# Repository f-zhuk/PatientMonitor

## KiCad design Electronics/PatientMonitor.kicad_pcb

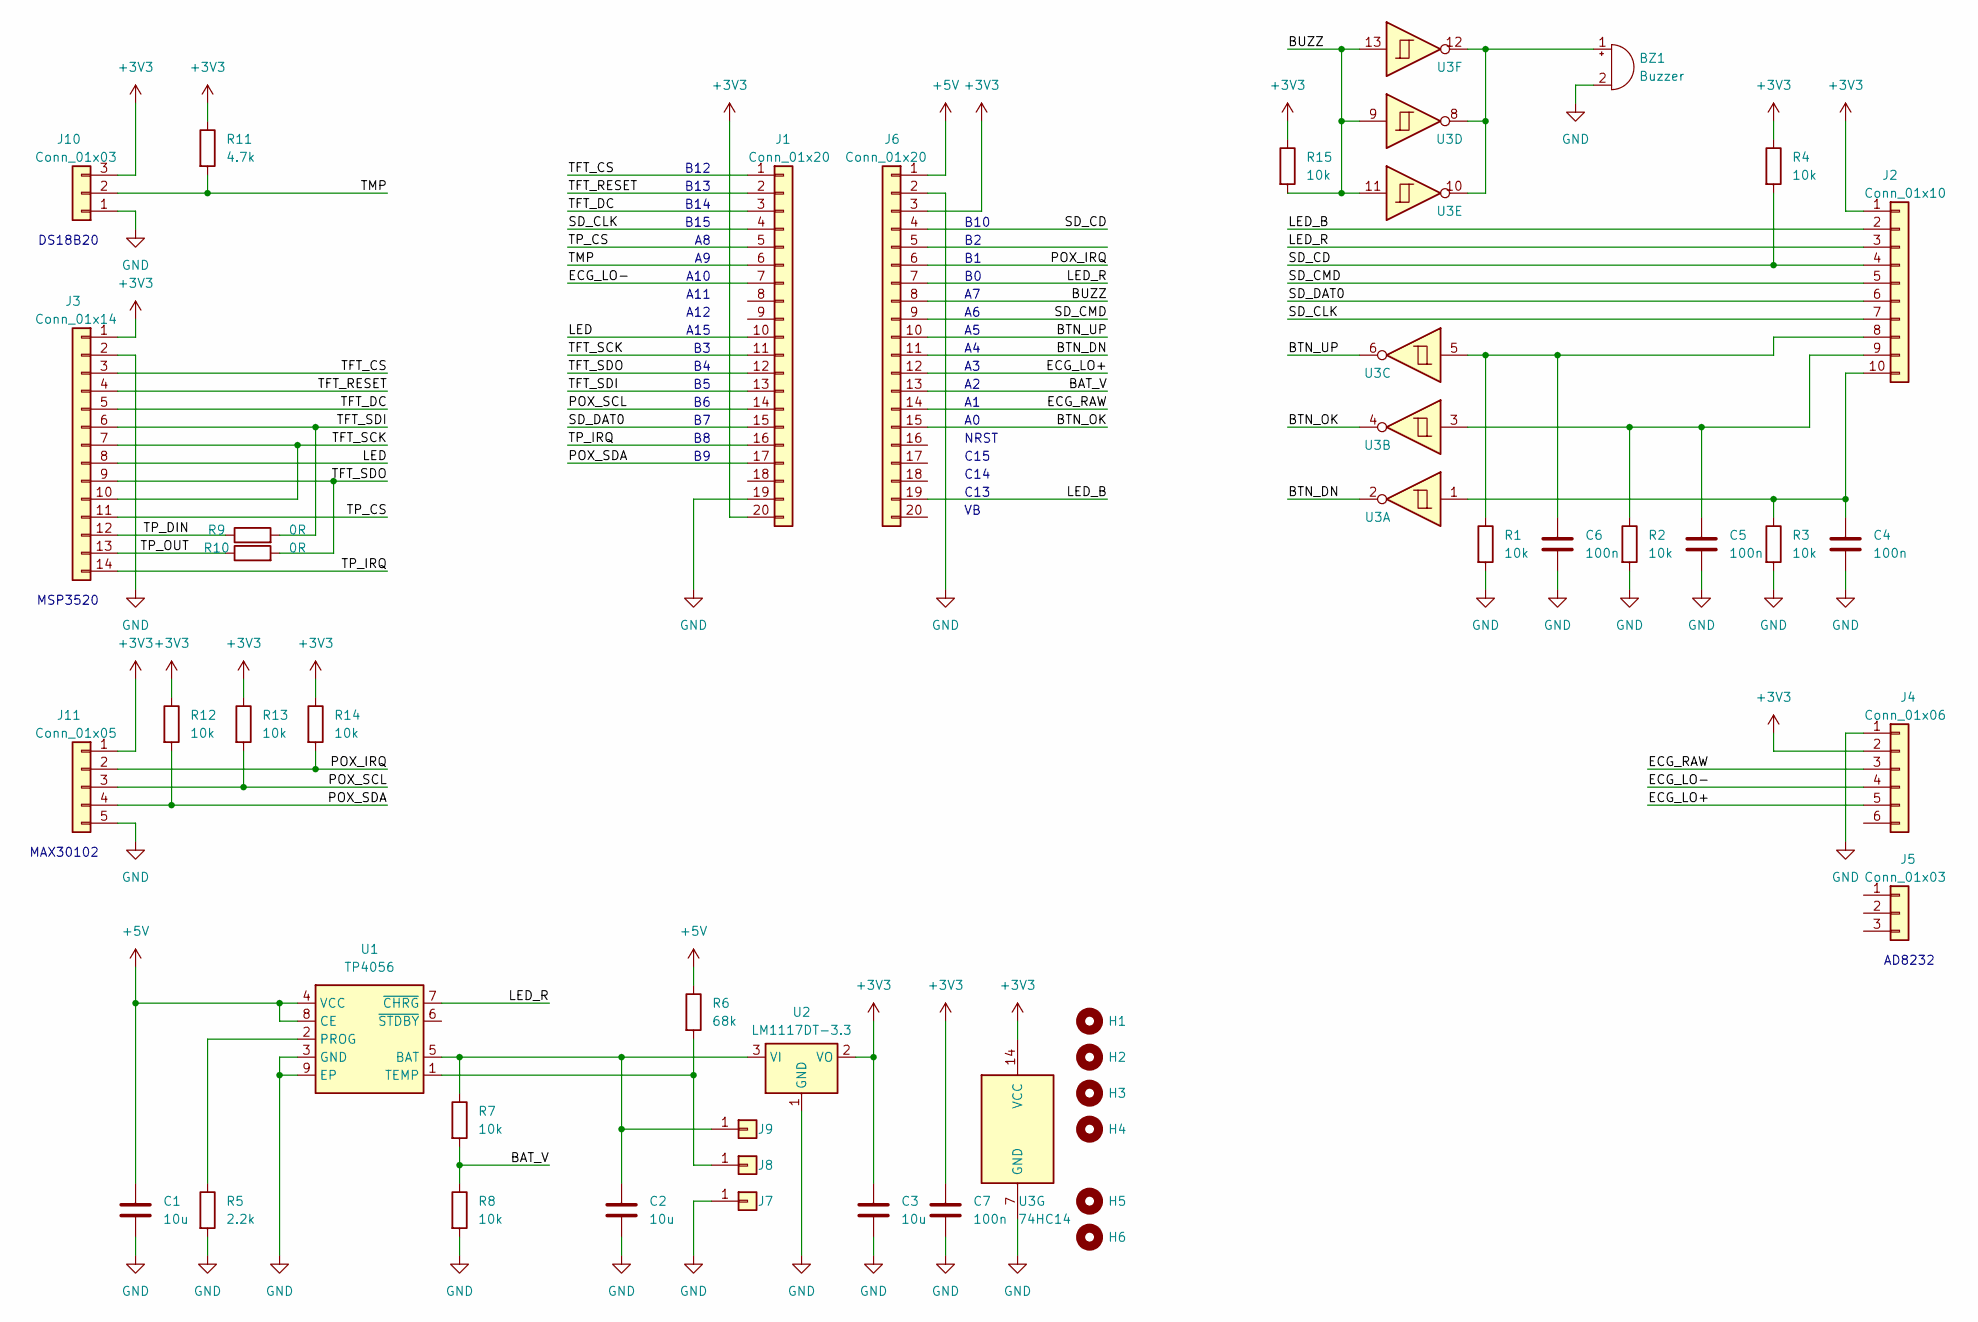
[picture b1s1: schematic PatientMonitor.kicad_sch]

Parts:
BZ1: Buzzer; Buzzer_15x7.5RM7.6
C1, C2, C3: 10u; C_0805_2012Metric_Pad1.18x1.45mm_HandSolder
C4, C5, C6, C7: 100n; C_0603_1608Metric_Pad1.08x0.95mm_HandSolder
H1, H2, H3, H4: MountingHole; MountingHole_3.2mm_M3
H5, H6: MountingHole; MountingHole_3.2mm_M3_Pad
J1, J6: Conn_01x20; PinSocket_1x20_P2.54mm_Vertical
J2: Conn_01x10; PinSocket_1x10_P2.54mm_Vertical
J3: Conn_01x14; PinSocket_1x14_P2.54mm_Vertical
J4: Conn_01x06; PinSocket_1x06_P2.54mm_Vertical
J5, J10: Conn_01x03; PinSocket_1x03_P2.54mm_Vertical
J7, J8, J9: Conn_01x01; SolderWire-0.5sqmm_1x01_D0.9mm_OD2.3mm
J11: Conn_01x05; PinHeader_1x05_P2.54mm_Vertical
R1, R2, R3, R4, R7, R8, R12, R13, R14, R15: 10k; R_0603_1608Metric_Pad0.98x0.95mm_HandSolder
R5: 2.2k; R_0603_1608Metric_Pad0.98x0.95mm_HandSolder
R6: 68k; R_0603_1608Metric_Pad0.98x0.95mm_HandSolder
R9, R10: 0R; R_0603_1608Metric_Pad0.98x0.95mm_HandSolder
R11: 4.7k; R_0603_1608Metric_Pad0.98x0.95mm_HandSolder
U1: TP4056; SOIC-8-1EP_3.9x4.9mm_P1.27mm_EP2.29x3mm
U2: LM1117DT-3.3; TO-252-2
U3: 74HC14; SO-14_3.9x8.65mm_P1.27mm

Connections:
+3V3: C3.1, C7.1, J1.20, J2.1, J3.1, J4.2, J6.3, J10.3, J11.1, R4.1, R11.1, R12.1, R13.1, R14.1, R15.1, U2.2 (VO), U3.14 (VCC)
+5V: C1.1, J6.1, R6.1, U1.4 (VCC), U1.8 (CE)
/BAT_V: J6.13, R7.2, R8.1
/BTN_DN: J6.11, U3.2
/BTN_OK: J6.15, U3.4
/BTN_UP: J6.10, U3.6
/BUZZ: J6.8, R15.2, U3.9, U3.11, U3.13
/ECG_LO+: J4.5, J6.12
/ECG_LO-: J1.7, J4.4
/ECG_RAW: J4.3, J6.14
/LED: J1.10, J3.8
/LED_B: J2.2, J6.19
/LED_R: J2.3, J6.7, U1.7 (~CHRG)
/POX_IRQ: J6.6, J11.2, R14.2
/POX_SCL: J1.14, J11.3, R13.2
/POX_SDA: J1.17, J11.4, R12.2
/SD_CD: J2.4, J6.4, R4.2
/SD_CLK: J1.4, J2.7
/SD_CMD: J2.5, J6.9
/SD_DAT0: J1.15, J2.6
/TFT_CS: J1.1, J3.3
/TFT_DC: J1.3, J3.5
/TFT_RESET: J1.2, J3.4
/TFT_SCK: J1.11, J3.7, J3.10
/TFT_SDI: J1.13, J3.6, R9.2
/TFT_SDO: J1.12, J3.9, R10.2
/TMP: J1.6, J10.2, R11.2
/TP_CS: J1.5, J3.11
/TP_DIN: J3.12, R9.1
/TP_IRQ: J1.16, J3.14
/TP_OUT: J3.13, R10.1
GND: BZ1.2 (-), C1.2, C2.2, C3.2, C4.2, C5.2, C6.2, C7.2, J1.19, J3.2, J4.1, J6.2, J7.1, J10.1, J11.5, R1.2, R2.2, R3.2, R5.2, R8.2, U1.3 (GND), U1.9 (EP), U2.1 (GND), U3.7 (GND)
unnamed: BZ1.1 (+), U3.8, U3.10, U3.12
unnamed: C6.1, J2.8, R1.1, U3.5
unnamed: C5.1, J2.9, R2.1, U3.3
unnamed: C4.1, J2.10, R3.1, U3.1
unnamed: J8.1, R6.2, U1.1 (TEMP)
unnamed: C2.1, J9.1, R7.1, U1.5 (BAT), U2.3 (VI)
unnamed: R5.1, U1.2 (PROG)

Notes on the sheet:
B15
A11
MSP3520
A12
AD8232
B13
B14
MAX30102
NRST
C13
C15
B10
B12
A15
A10
DS18B20
C14

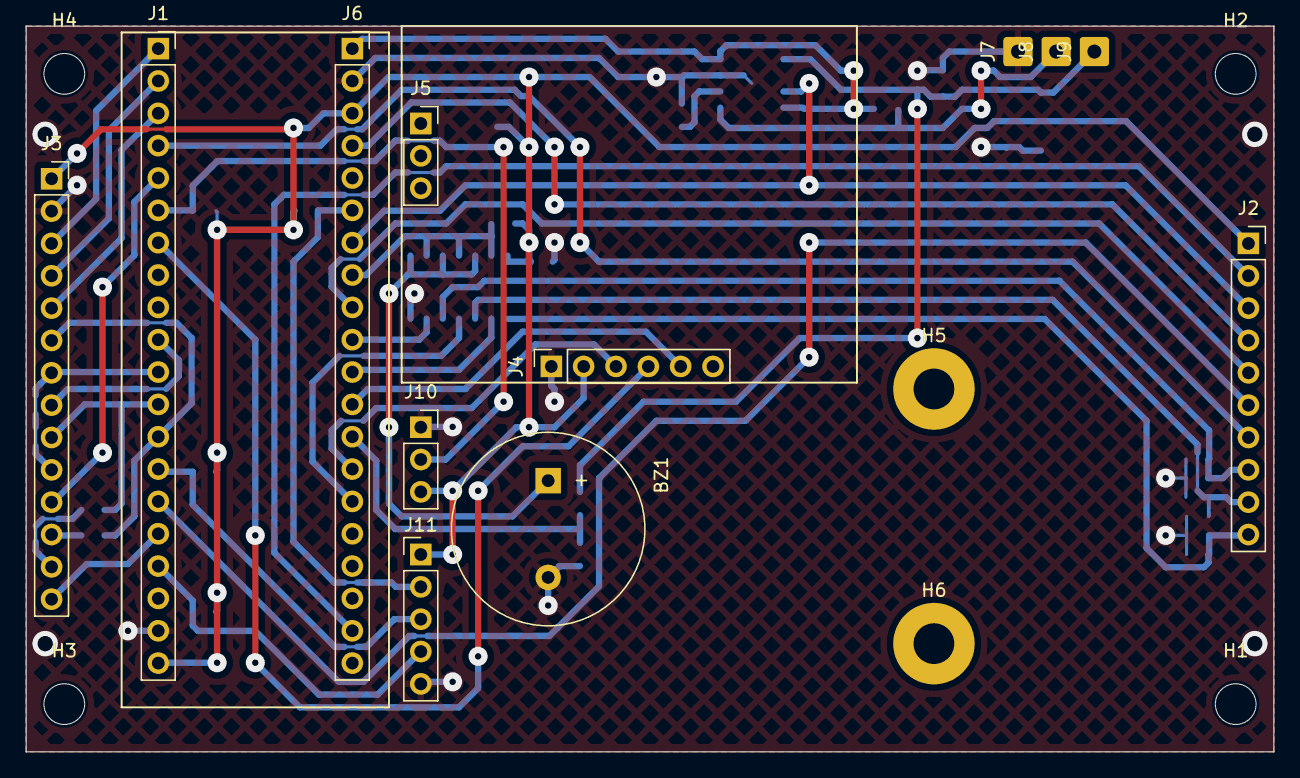
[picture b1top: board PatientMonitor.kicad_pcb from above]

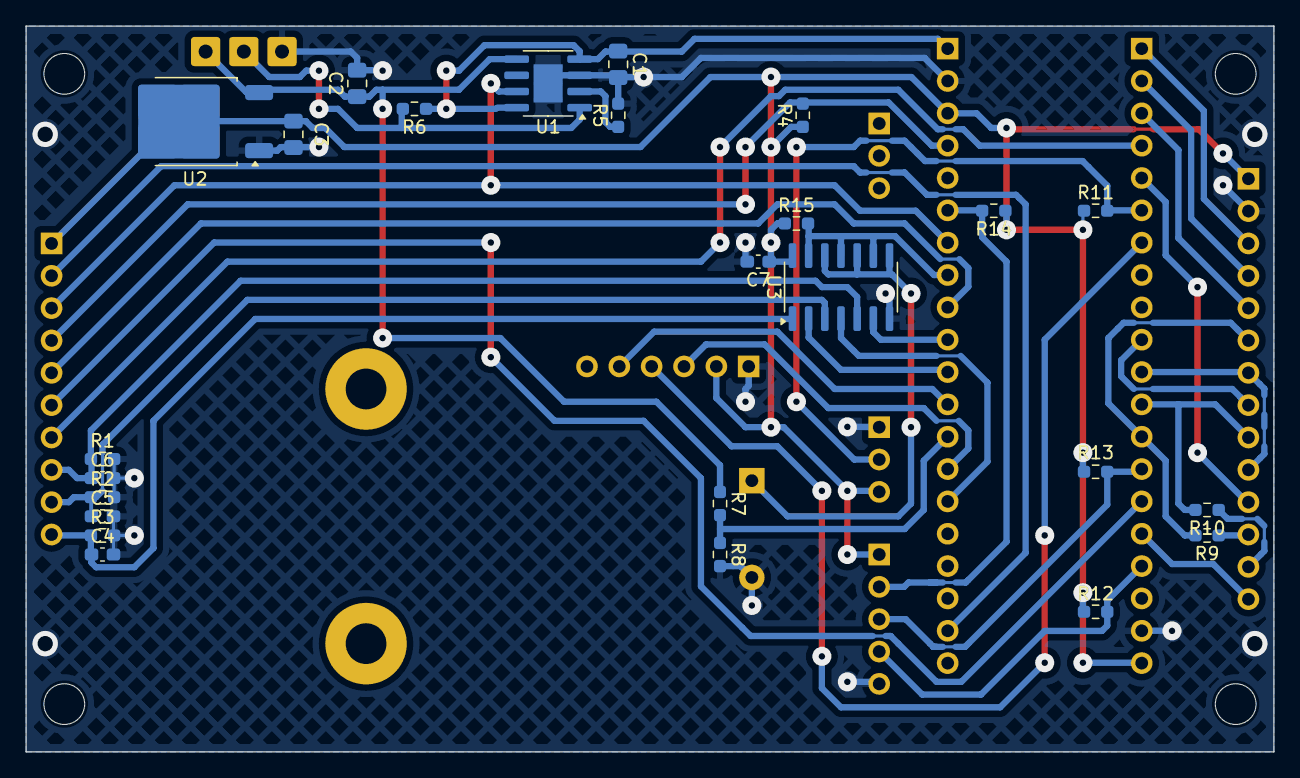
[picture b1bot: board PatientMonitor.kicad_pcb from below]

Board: 2 copper layers, 98.0 x 57.0 mm, 43 parts (25 on the bottom side), 39 nets.

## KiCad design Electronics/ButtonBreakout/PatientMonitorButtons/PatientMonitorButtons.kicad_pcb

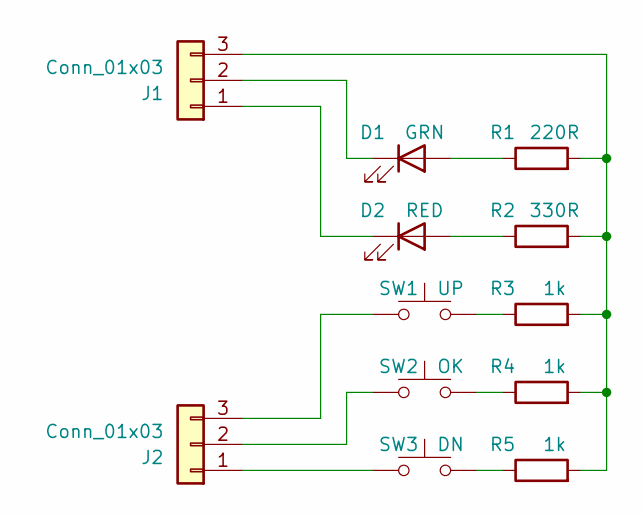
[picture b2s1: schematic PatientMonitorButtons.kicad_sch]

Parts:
D1: GRN; LED_0805_2012Metric_Pad1.15x1.40mm_HandSolder
D2: RED; LED_0805_2012Metric_Pad1.15x1.40mm_HandSolder
J1, J2: Conn_01x03; PinHeader_1x03_P2.54mm_Horizontal
R1: 220R; R_0603_1608Metric_Pad0.98x0.95mm_HandSolder
R2: 330R; R_0603_1608Metric_Pad0.98x0.95mm_HandSolder
R3, R4, R5: 1k; R_0603_1608Metric_Pad0.98x0.95mm_HandSolder
SW1: UP; SW_SPST_CK_PTS641
SW2: OK; SW_SPST_CK_PTS641
SW3: DN; SW_SPST_CK_PTS641

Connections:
unnamed: D1.2 (A), R1.1
unnamed: D1.1 (K), J1.2
unnamed: D2.2 (A), R2.1
unnamed: D2.1 (K), J1.1
unnamed: J1.3, R1.2, R2.2, R3.2, R4.2, R5.2
unnamed: J2.1, SW3.1
unnamed: J2.2, SW2.1
unnamed: J2.3, SW1.1
unnamed: R3.1, SW1.2
unnamed: R4.1, SW2.2
unnamed: R5.1, SW3.2

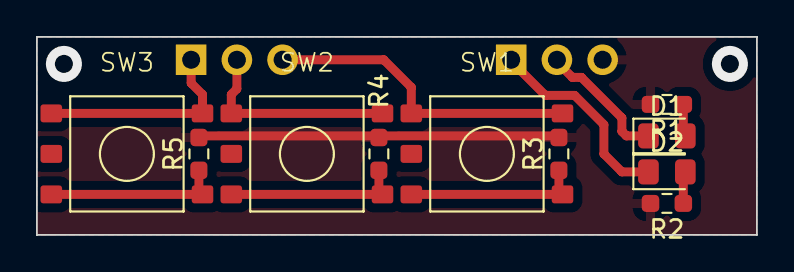
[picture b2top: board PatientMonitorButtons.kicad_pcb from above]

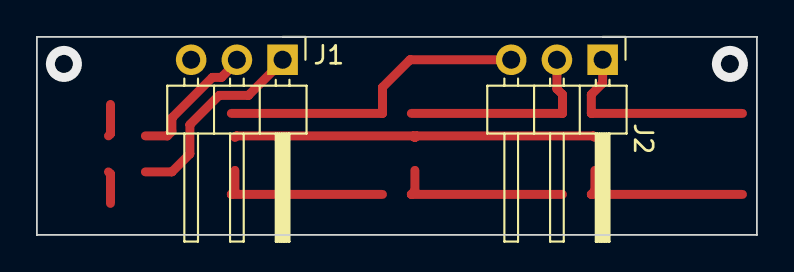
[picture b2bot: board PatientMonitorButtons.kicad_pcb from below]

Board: 2 copper layers, 40.0 x 11.0 mm, 12 parts (2 on the bottom side), 11 nets.

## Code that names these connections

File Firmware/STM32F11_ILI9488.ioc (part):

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Mcu.Name=STM32F411C(C-E)Ux
Mcu.Package=UFQFPN48
Mcu.UserName=STM32F411CEUx
PA0-WKUP.GPIOParameters=GPIO_Label
PA0-WKUP.GPIO_Label=BTN_OK
PA0-WKUP.Mode=SYS_WakeUp0
PA0-WKUP.Signal=SYS_WKUP
PA1.GPIOParameters=GPIO_Label
PA1.GPIO_Label=ECG_RAW
PA1.Signal=ADCx_IN1
PA10.GPIOParameters=GPIO_Label
PA10.GPIO_Label=LON
PA10.Signal=GPIO_Input
PA11.Mode=Device_Only
PA11.Signal=USB_OTG_FS_DM
PA12.Mode=Device_Only
PA12.Signal=USB_OTG_FS_DP
PA13.Mode=Serial_Wire
PA13.Signal=SYS_JTMS-SWDIO
PA14.Mode=Serial_Wire
PA14.Signal=SYS_JTCK-SWCLK
PA15.GPIOParameters=GPIO_Label
PA15.GPIO_Label=LED
PA15.Signal=S_TIM2_CH1_ETR
PA2.GPIOParameters=GPIO_Label
PA2.GPIO_Label=BAT_V
PA2.Signal=ADCx_IN2
PA3.GPIOParameters=GPIO_Label
PA3.GPIO_Label=LOP
PA3.Signal=GPIO_Input
PA4.GPIOParameters=GPIO_Label
PA4.GPIO_Label=BTN_DN
PA4.Signal=GPIO_Input
PA5.GPIOParameters=GPIO_Label
PA5.GPIO_Label=BTN_UP
PA5.Signal=GPIO_Input
PA6.Mode=SD_1_bit
PA6.Signal=SDIO_CMD
PA7.GPIOParameters=GPIO_Label
PA7.GPIO_Label=BUZZ
PA7.Signal=S_TIM3_CH2
PA8.GPIOParameters=GPIO_Label
PA8.GPIO_Label=TP_CS
PA8.Signal=GPIO_Output
PA9.GPIOParameters=GPIO_Label
PA9.GPIO_Label=TMP
PA9.Mode=Half_duplex(single_wire_mode)
PA9.Signal=USART1_TX
PB0.GPIOParameters=GPIO_Label
PB0.GPIO_Label=LED_R
PB0.Signal=GPIO_Input
PB1.GPIOParameters=GPIO_Label
PB1.GPIO_Label=POX_IRQ
PB1.Signal=GPXTI1
PB10.GPIOParameters=GPIO_Label
PB10.GPIO_Label=SD_CD
PB10.Signal=GPIO_Input
PB12.GPIOParameters=GPIO_Label
PB12.GPIO_Label=TFT_CS
PB12.Signal=GPIO_Output
PB13.GPIOParameters=GPIO_Label
PB13.GPIO_Label=TFT_RST
PB13.Signal=GPIO_Output
PB14.GPIOParameters=GPIO_Label
PB14.GPIO_Label=TFT_DC
PB14.Signal=GPIO_Output
PB15.Mode=SD_1_bit
PB15.Signal=SDIO_CK
PB3.Mode=Full_Duplex_Master
PB3.Signal=SPI1_SCK
PB4.Mode=Full_Duplex_Master
PB4.Signal=SPI1_MISO
PB5.Mode=Full_Duplex_Master
PB5.Signal=SPI1_MOSI
PB6.Mode=I2C
PB6.Signal=I2C1_SCL
PB7.Mode=SD_1_bit
PB7.Signal=SDIO_D0
PB8.GPIOParameters=GPIO_Label
PB8.GPIO_Label=TP_IRQ
PB8.Signal=GPXTI8
PB9.Mode=I2C
PB9.Signal=I2C1_SDA
PC13-ANTI_TAMP.GPIOParameters=PinState,GPIO_Label
PC13-ANTI_TAMP.GPIO_Label=LED_B
PC13-ANTI_TAMP.PinState=GPIO_PIN_RESET
PC13-ANTI_TAMP.Signal=GPIO_Output
PC14-OSC32_IN.Mode=LSE-External-Oscillator
PC14-OSC32_IN.Signal=RCC_OSC32_IN
PC15-OSC32_OUT.Mode=LSE-External-Oscillator
PC15-OSC32_OUT.Signal=RCC_OSC32_OUT
PH0\ -\ OSC_IN.Mode=HSE-External-Oscillator
PH0\ -\ OSC_IN.Signal=RCC_OSC_IN
PH1\ -\ OSC_OUT.Mode=HSE-External-Oscillator
PH1\ -\ OSC_OUT.Signal=RCC_OSC_OUT
RCC.HSE_VALUE=25000000
RCC.SYSCLKFreq_VALUE=100000000
RCC.SYSCLKSource=RCC_SYSCLKSOURCE_PLLCLK
board=custom

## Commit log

2024-06-10 Initial upload for history
2024-06-11 Visuals and STM32CUBE config added
2024-07-20 No changes on purpose
